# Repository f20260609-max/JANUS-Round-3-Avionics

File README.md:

#SUMMARY OF WHATEVER I DID.

##Task 1
### for task 1 i asked AI to write me the code and I understood it properly from Genmini... from what i understood... the Digi X bee is a radio transmitter which relays our signals from our compiuter to the cansat or drone or wytv is up in the air...
### here's what i understood about the functions being used in my code - 
parse_telemetry_packet(raw_data) #### this function unpacks the text data which is sent from our computer...it splits the string up and reads the correspongig indexes for altitude,latitude and longitude..
dummy_telemetry_generator() #### it basically helps us run a simulation without needing a real drone...
xbee_callback(xbee_message) #### this is used when hardware is being used... it basically is the radio reciever of the whole code 
update_plot(frame) #### as evidenced by the name... it helps with the plotting of the graph... 

##Task 2 
### for task 2 i have also used ai to get a gist of the requirements and used it to write the code.... 
parafoil_derivatives(state, delta_a, wind) #### basically helps us understand the location of the glider and the factors acting on it.(calculates the aerodynamic moments and all and uses it to calculate the forward sink speed and all that.)
compute_control(x, y, psi, target, kp, kd, r)... and the rest im lowk skipping out on since time is running out.... but rest assured i have studied up on it.

##Task3 
### I lowk gave up on it task after spending some 1.25 hours on it trying to figure out how to open and save and rearrange and connect but ultimately the edge board wasn't shwoing aso i just gave up... but yea... interesting exp fr..

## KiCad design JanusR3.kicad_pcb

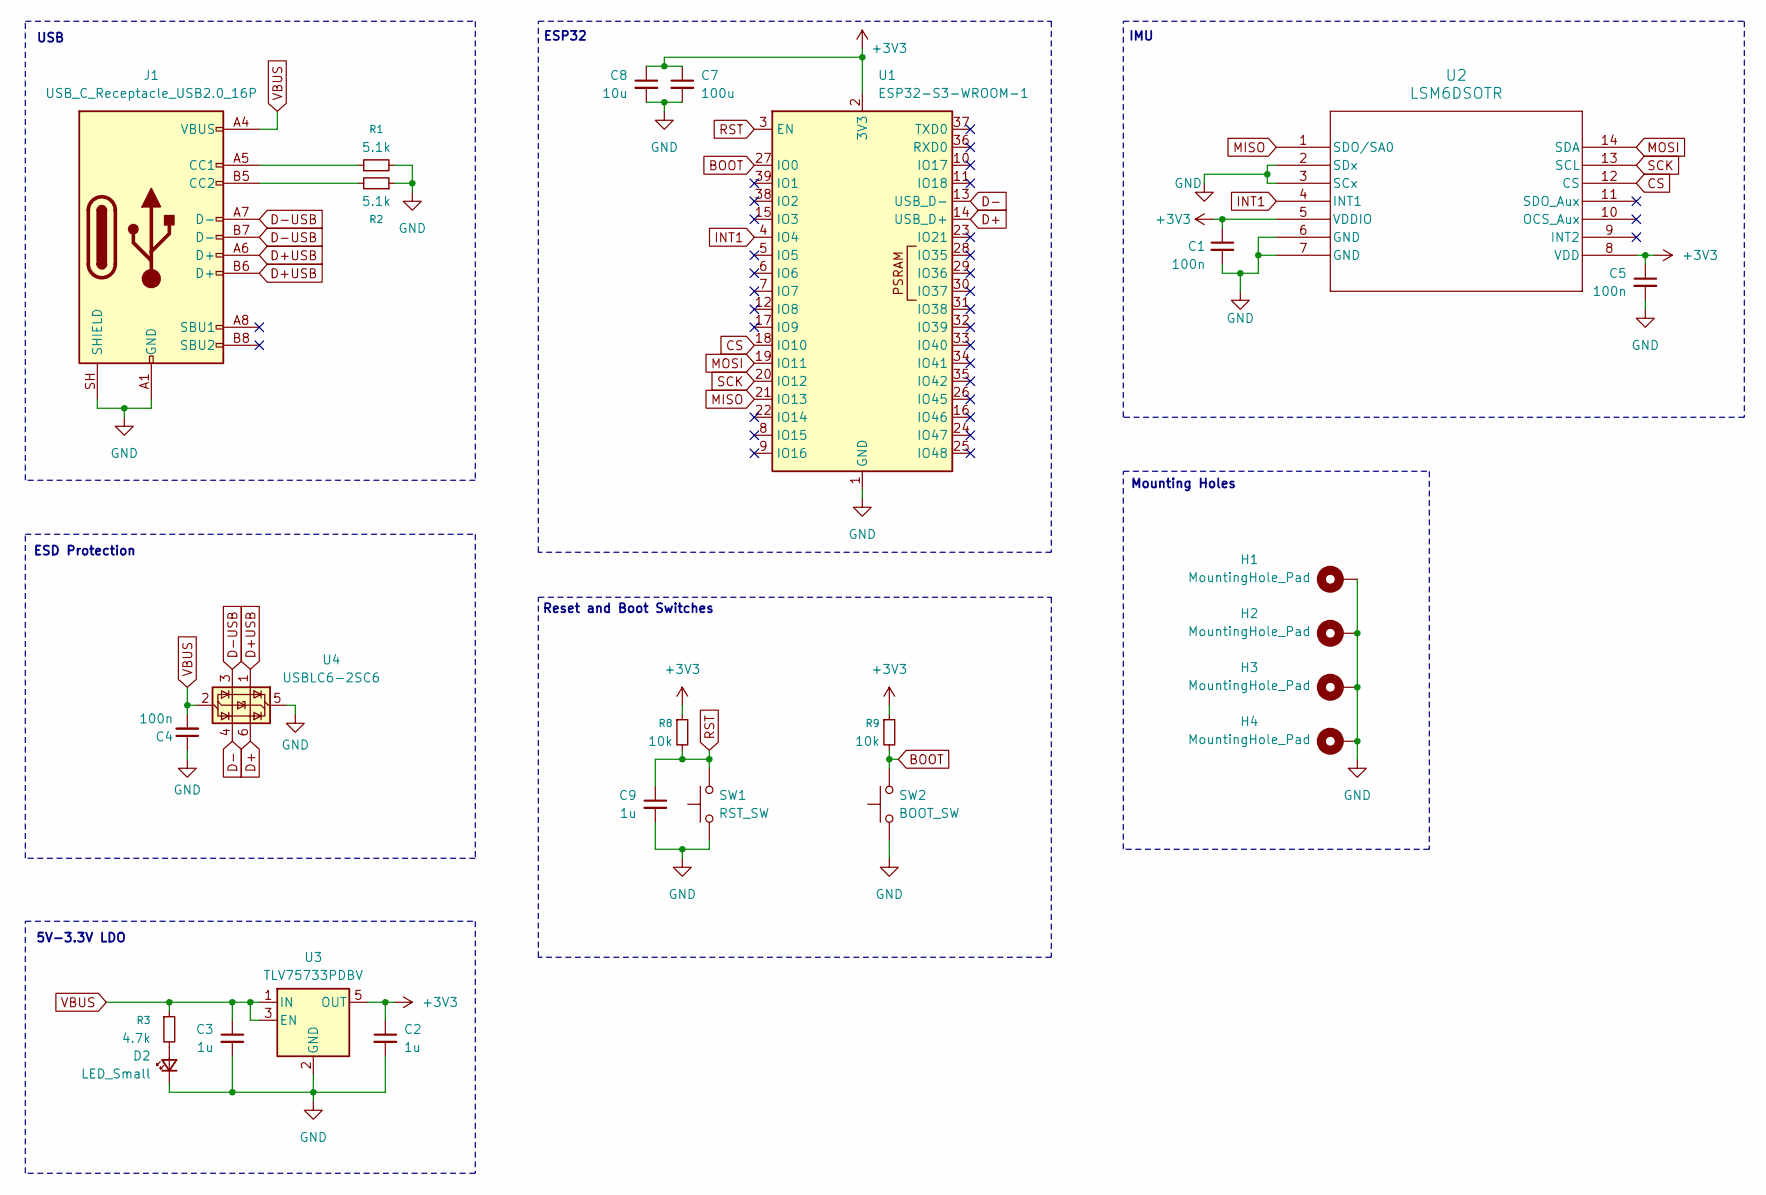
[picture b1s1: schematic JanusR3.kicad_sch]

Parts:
C1, C4, C5: 100n; C_0805_2012Metric_Pad1.18x1.45mm_HandSolder
C2, C3, C9: 1u; C_0805_2012Metric_Pad1.18x1.45mm_HandSolder
C7: 100u; C_0805_2012Metric_Pad1.18x1.45mm_HandSolder
C8: 10u; C_0805_2012Metric_Pad1.18x1.45mm_HandSolder
D2: LED_Small; LED_0805_2012Metric_Pad1.15x1.40mm_HandSolder
H1, H2, H3, H4: MountingHole_Pad; MountingHole_2.2mm_M2_Pad_Via
J1: USB_C_Receptacle_USB2.0_16P; USB_C_Receptacle_GCT_USB4105-xx-A_16P_TopMnt_Horizontal
R1, R2: 5.1k; R_0805_2012Metric_Pad1.20x1.40mm_HandSolder
R3: 4.7k; R_0805_2012Metric_Pad1.20x1.40mm_HandSolder
R8, R9: 10k; R_0805_2012Metric_Pad1.20x1.40mm_HandSolder
SW1: RST_SW; SW_Push_1P1T_NO_CK_KMR2
SW2: BOOT_SW; SW_Push_1P1T_NO_CK_KMR2
U1: ESP32-S3-WROOM-1
U2: LSM6DSOTR; Texas_S-PX2QFN-14
U3: TLV75733PDBV; SOT-23-5
U4: USBLC6-2SC6; SOT-23-6

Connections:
+3V3: C1.1, C2.1, C5.1, C7.1, C8.1, R8.1, R9.1, U1.2 (3V3), U2.5 (VDDIO), U2.8 (VDD), U3.5 (OUT)
BOOT: R9.2, SW2.2, U1.27 (IO0)
CS: U1.18 (IO10), U2.12 (CS)
D+: U1.14 (USB_D+), U4.6 (I/O1)
D+USB: J1.A6 (D+), J1.B6 (D+), U4.1 (I/O1)
D-: U1.13 (USB_D-), U4.4 (I/O2)
D-USB: J1.A7 (D-), J1.B7 (D-), U4.3 (I/O2)
GND: C1.2, C2.2, C3.2, C4.1, C5.2, C7.2, C8.2, C9.2, D2.1 (K), H1.1 (1_1), H2.1 (1_1), H3.1 (1_1), H4.1 (1_1), J1.A1 (GND), J1.A12 (GND), J1.B1 (GND), J1.B12 (GND), J1.SH (SHIELD), R1.2, R2.1, SW1.1, SW2.1, U1.1 (GND), U1.40 (GND), U1.41 (GND), U2.2 (SDx), U2.3 (SCx), U2.6 (GND), U2.7 (GND), U3.2 (GND), U4.5 (VBUS)
INT1: U1.4 (IO4), U2.4 (INT1)
MISO: U1.21 (IO13), U2.1 (SDO/SA0)
MOSI: U1.19 (IO11), U2.14 (SDA)
unnamed: D2.2 (A), R3.2
unnamed: J1.A5 (CC1), R1.1
unnamed: J1.B5 (CC2), R2.2
RST: C9.1, R8.2, SW1.2, U1.3 (EN)
SCK: U1.20 (IO12), U2.13 (SCL)
VBUS: C3.1, C4.2, J1.A4 (VBUS), J1.A9 (VBUS), J1.B4 (VBUS), J1.B9 (VBUS), R3.1, U3.1 (IN), U3.3 (EN), U4.2 (GND)

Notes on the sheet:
5V-3.3V LDO
Reset and Boot Switches
ESP32
IMU
ESD Protection
USB
Mounting Holes

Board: 2 copper layers, 25 parts (0 on the bottom side), 17 nets, no tracks yet.
